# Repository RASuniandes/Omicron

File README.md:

<h1 align="center">RAS Uniandes  - Omicron (Mini-Sumo 🤖)</h1>

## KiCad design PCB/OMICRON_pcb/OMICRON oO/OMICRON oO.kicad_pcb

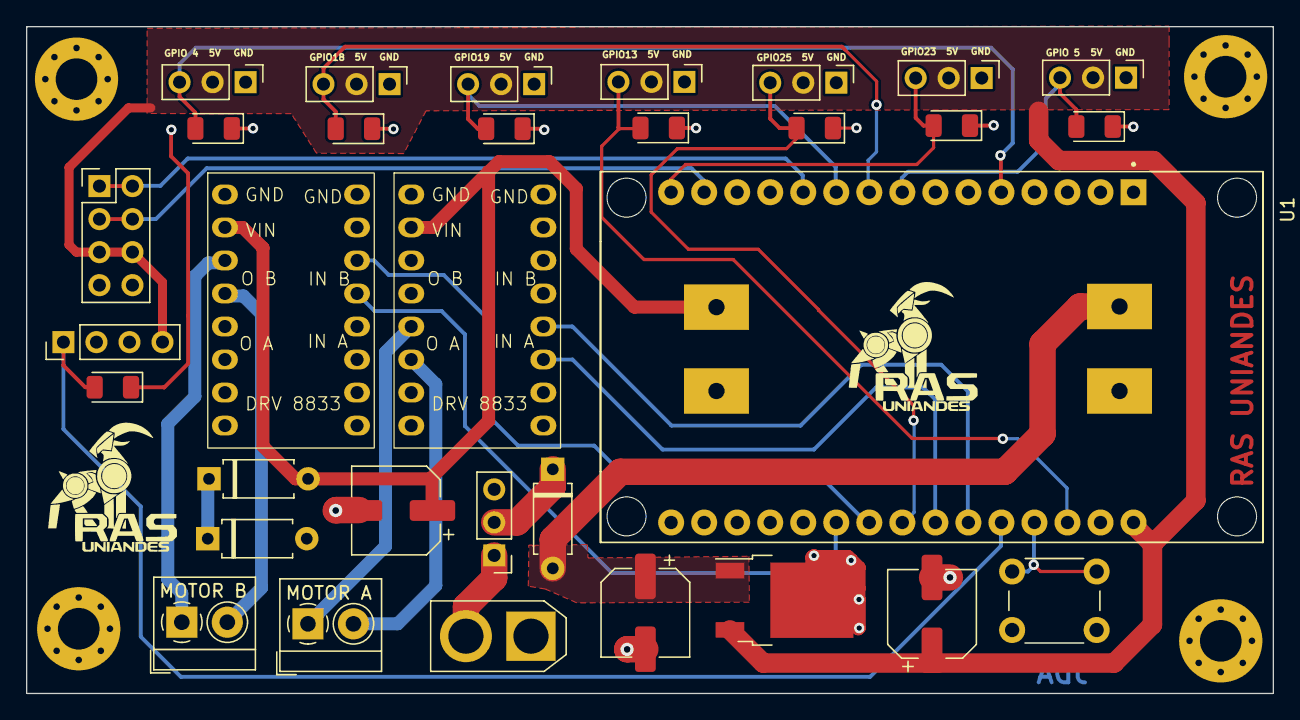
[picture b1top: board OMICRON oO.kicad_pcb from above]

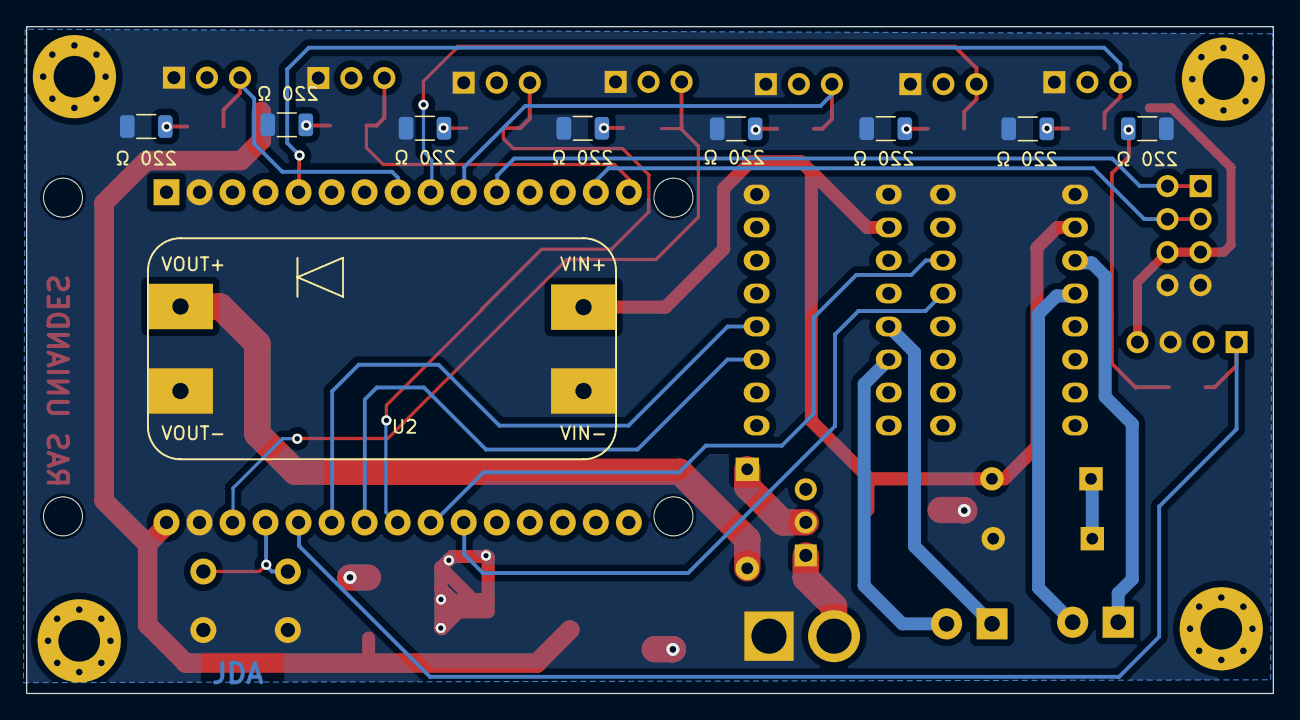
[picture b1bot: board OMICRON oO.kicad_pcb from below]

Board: 2 copper layers, 95.9 x 51.3 mm, 45 parts (9 on the bottom side), 34 nets.

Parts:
C1: 100 μF; CP_Elec_6.3x5.9
C3: 0.33; CP_Elec_6.3x5.9
C4: 0.1; CP_Elec_6.3x5.9
D1, D2: D_Zener; D_A-405_P7.62mm_Horizontal
D3, D4, D5, D6, D8, D9, D10, D11: LED; LED_1206_3216Metric
D7: DIODE; D_A-405_P7.62mm_Horizontal
DRV 8833, DRV 8833#2: DRV 8833
H1, H2, H3, H4: MountingHole; MountingHole_3.2mm_M3_Pad_Via
J1: VCC; AMASS_XT30U-F_1x02_P5.0mm_Vertical
J2, J3, J4, J5, J6, J7, J8: JS40M (VISION); PinHeader_1x03_P2.54mm_Vertical
J9: MODULO STARTER; PinHeader_1x04_P2.54mm_Vertical
J10: I2C PROTOCOL; PinHeader_2x04_P2.54mm_Vertical
J11: MOTOR A; TerminalBlock_4Ucon_1x02_P3.50mm_Horizontal
J12: MOTOR B; TerminalBlock_4Ucon_1x02_P3.50mm_Horizontal
J13: Conn_02x01; SW_PUSH_6mm_H5mm
R1, R2, R3, R4, R5, R6, R7, R8: 220 Ω; R_1206_3216Metric
SW1: SW_SPDT; PinHeader_1x03_P2.54mm_Vertical
U1: ESP32-DEVKIT-V1; MODULE_ESP32_DEVKIT_V1
U2: MT3608_module
U3: LM7805; TO-252-2

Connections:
+5V: C4.1, J2.2, J3.2, J4.2, J5.2, J6.2, J7.2, J8.2, J9.4, J10.5, J10.6, U1.30 (VIN), U3.3 (VO)
GND: C1.2, C3.2, C4.2, D2.2 (A), DRV 8833.1 (GND), DRV 8833.9 (GND), DRV 8833#2.1 (GND), DRV 8833#2.9 (GND), J1.1 (Pin_2), J2.1, J3.1, J4.1, J5.1, J6.1, J7.1, J8.1, J9.3, J10.7, J10.8, J13.2, R1.2, R2.2, R3.2, R4.2, R5.2, R6.2, R7.2, R8.2, U1.2 (GND), U1.29 (GND), U2.2 (VOUT_-), U2.3 (VIN_-), U3.2 (GND)
GPIO 4: D3.2 (A), J2.3, U1.5 (D4)
GPIO 5: D8.2 (A), J3.3, U1.8 (D5)
GPIO 12: J13.1, U1.27 (D12)
GPIO 13: D9.2 (A), J4.3, U1.28 (D13)
GPIO 14: D5.2 (A), J9.1, U1.26 (D14)
GPIO 18: D10.2 (A), J5.3, U1.9 (D18)
GPIO 19: D4.2 (A), J6.3, U1.10 (D19)
GPIO 23: D6.2 (A), J7.3, U1.15 (D23)
GPIO 25: D11.2 (A), J8.3, U1.23 (D25)
MOTOR A1: DRV 8833.13 (IN_A2), U1.25 (D27)
MOTOR A2: DRV 8833.14 (IN_A1), U1.24 (D26)
MOTOR B1: DRV 8833#2.11 (IN_B1), U1.22 (D33)
MOTOR B2: DRV 8833#2.12 (IN_B2), U1.21 (D32)
unnamed: D1.1 (K), D2.1 (K)
unnamed: D3.1 (K), R1.1
unnamed: D4.1 (K), R2.1
unnamed: D5.1 (K), R3.1
unnamed: D6.1 (K), R4.1
unnamed: D7.1 (K), SW1.2 (B)
unnamed: D8.1 (K), R5.1
unnamed: D9.1 (K), R6.1
unnamed: D10.1 (K), R7.1
unnamed: D11.1 (K), R8.1
unnamed: J1.2 (Pin_1), SW1.1 (A)
OUT A1: DRV 8833.5 (OUT_A2), J11.1
OUT A2: DRV 8833.6 (OUT_A1), J11.2
OUT B1: DRV 8833#2.3 (OUT_B1), J12.1
OUT B2: DRV 8833#2.4 (OUT_B2), J12.2
SCL: J10.3, J10.4, U1.14 (D22)
SDA: J10.1, J10.2, U1.11 (D21)
VCC: C3.1, D7.2 (A), U2.4 (VIN_+), U3.1 (VI)
VIN M: C1.1, D1.2 (A), DRV 8833.2 (VIN), DRV 8833#2.2 (VIN), U2.1 (VOUT_+)

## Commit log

2023-08-23 Instanciación de las primeras clases
2023-08-23 Carpeta del diseño de PCB Omicron
2023-08-23 Carpeta de documentación
2023-08-24 Motores
2023-08-24 Setup_sensors
2023-08-24 Funcion de ponderación
2023-08-24 PID 1
2023-08-24 tracking
2023-08-24 security code
2023-08-24 test_tracking PID
2023-08-26 Starter
2023-08-26 Starter and Stop
2023-08-27 PID Finalizado, falta calibrar
2023-08-28 PID_working 120_speed
2023-08-28 1-iteraton qtr
2023-08-28 change pid
2023-08-28 original constant
2023-08-31 game_rules finish
2023-09-05 Mis ultimos cambios BCJH
2023-09-12 COmmit before pull
2023-09-12 Archivos de la PCB Omicron
2023-10-02 To the from
2023-10-11 Corrección del tipado de variables, y calibración de getIn con los nuevos motores
2023-10-12 Calibración PID más aproximada
2023-10-12 Zero control RC
2023-10-17 Versión semi-calibrada
2023-10-18 Código semi-calibrado
2023-10-20 Frenos de contorno (Implementación de la función)
2023-10-20 ultimos cambios
2023-10-20 cambios a joystick
2023-10-20 dios los quiera
2023-10-20 angulo de giro absoluto implementado
    full pal secso
2023-10-24 pruebas
2023-10-26 Frenos de contorno y calibracion PID
2023-10-30 ps3 demo
2023-11-07 strategies handler
2024-02-18 documentacion del codigo #1
    little changes for big problems
2024-10-10 Versión con posibles mejoras a probar
2024-10-13 Actualización de estructura y documentación
2024-10-13 Documentación Actualizada
